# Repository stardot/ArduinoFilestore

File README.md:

# ArduinoFilestore
Build an Econet filestore out of an Arduino Due, an SD and Ethernet shield, and an Acorn Econet module.

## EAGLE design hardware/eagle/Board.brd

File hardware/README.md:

# Assembling the Arduino FileStore
The project is based around the [Arduino Due](https://store.arduino.cc/arduino-due) board, fitted with an SD card and Ethernet shield. The Due was chosen because of the combination of IO pin availability, and the speed of the 32Bit Arm processor on-board.

This is interfaced to an Acorn ADF10 (or AEH52) Econet module of the type normally used to upgrade a BBC Master, Acorn Archimedes or A Series machine with Econet connectivity. Only the Acorn upgrade cards have been tested and confirmed to work. The HCCS Econet module was found not to work when tested.

The Econet module and Arduino have their data bus linked via a SN74LVC245A buffer which provides the bidirectional 5 to 3.3 volt translation. Other inputs to the Econet module are driven directly by the Arduino, and the IRQ output from the Econet module has a pull down resistor to reduce the voltage to a safe level for the Arduino. 

The 2Mhz clock is generated by the CPU timers on the Arduino, and is left to free run once configured. I've not found a reliable way of determining the clock phase by reading the CPU registers, and so the clock signal is looped back into a input pin on the Arduino.

The Eagle folder contains the schematic and board layout I used to produce a run of PCBs for the project. This layout only really works with the ADF10 module which has the long pins, you would need to move the Econet card headers clear of the DIN socket to be able to use the AEH52 module which has shorter pins. 

The Gerbers folder contains an archive of the files I sent to jlcpcb to make the PCBs for the project.

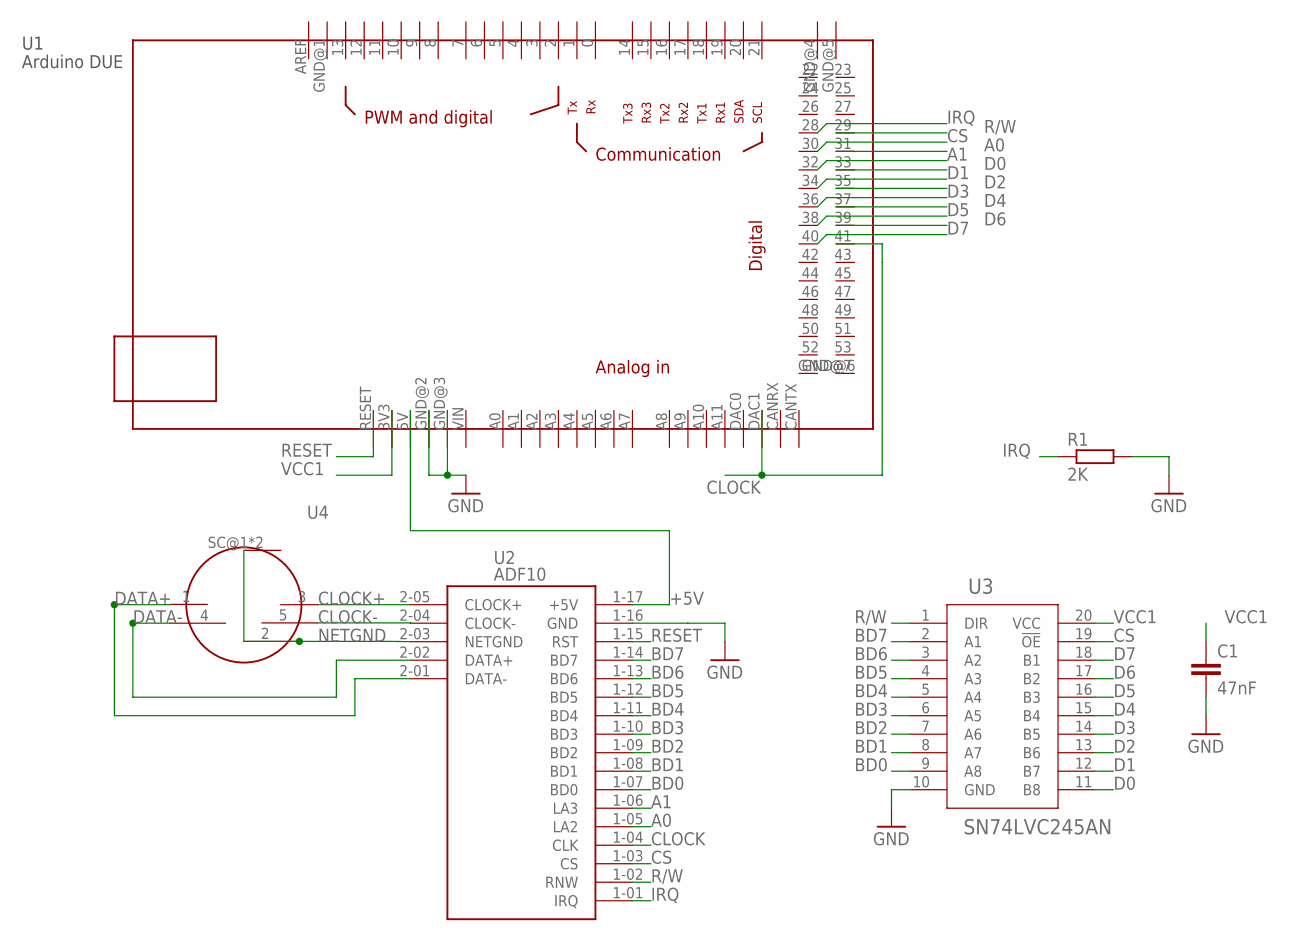
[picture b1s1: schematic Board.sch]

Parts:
C1: 47nF; C050-035X075
R1: 2K; 0309/12
U1: ARDUINODUE; MEGABOX
U2: ADF10
U3: SN74LVC245AN; N20
U4: 491087

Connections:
+5V: U1.5V, U2.1-17 (+5V)
A0: U1.31, U2.1-05 (LA2)
A1: U1.32, U2.1-06 (LA3)
BD0: U2.1-07 (BD0), U3.9 (A8)
BD1: U2.1-08 (BD1), U3.8 (A7)
BD2: U2.1-09 (BD2), U3.7 (A6)
BD3: U2.1-10 (BD3), U3.6 (A5)
BD4: U2.1-11 (BD4), U3.5 (A4)
BD5: U2.1-12 (BD5), U3.4 (A3)
BD6: U2.1-13 (BD6), U3.3 (A2)
BD7: U2.1-14 (BD7), U3.2 (A1)
CLOCK: U1.41, U1.DAC1, U2.1-04 (CLK)
CLOCK+: U2.2-05 (CLOCK+), U4.3
CLOCK-: U2.2-04 (CLOCK-), U4.5
CS: U1.30, U2.1-03 (CS), U3.19 (!OE)
D0: U1.33, U3.11 (B8)
D1: U1.34, U3.12 (B7)
D2: U1.35, U3.13 (B6)
D3: U1.36, U3.14 (B5)
D4: U1.37, U3.15 (B4)
D5: U1.38, U3.16 (B3)
D6: U1.39, U3.17 (B2)
D7: U1.40, U3.18 (B1)
DATA+: U2.2-01 (DATA-), U4.1
DATA-: U2.2-02 (DATA+), U4.4
GND: C1.2, R1.2, U1.GND@2 (GND), U1.GND@3 (GND), U2.1-16 (GND), U3.10 (GND)
IRQ: R1.1, U1.28, U2.1-01 (IRQ)
NETGND: U2.2-03 (NETGND), U4.2, U4.SC@1 (SHIELD), U4.SC@2 (SHIELD)
R/W: U1.29, U2.1-02 (RNW), U3.1 (DIR)
RESET: U1.RESET, U2.1-15 (RST)
VCC1: C1.1, U1.3V3, U3.20 (VCC)

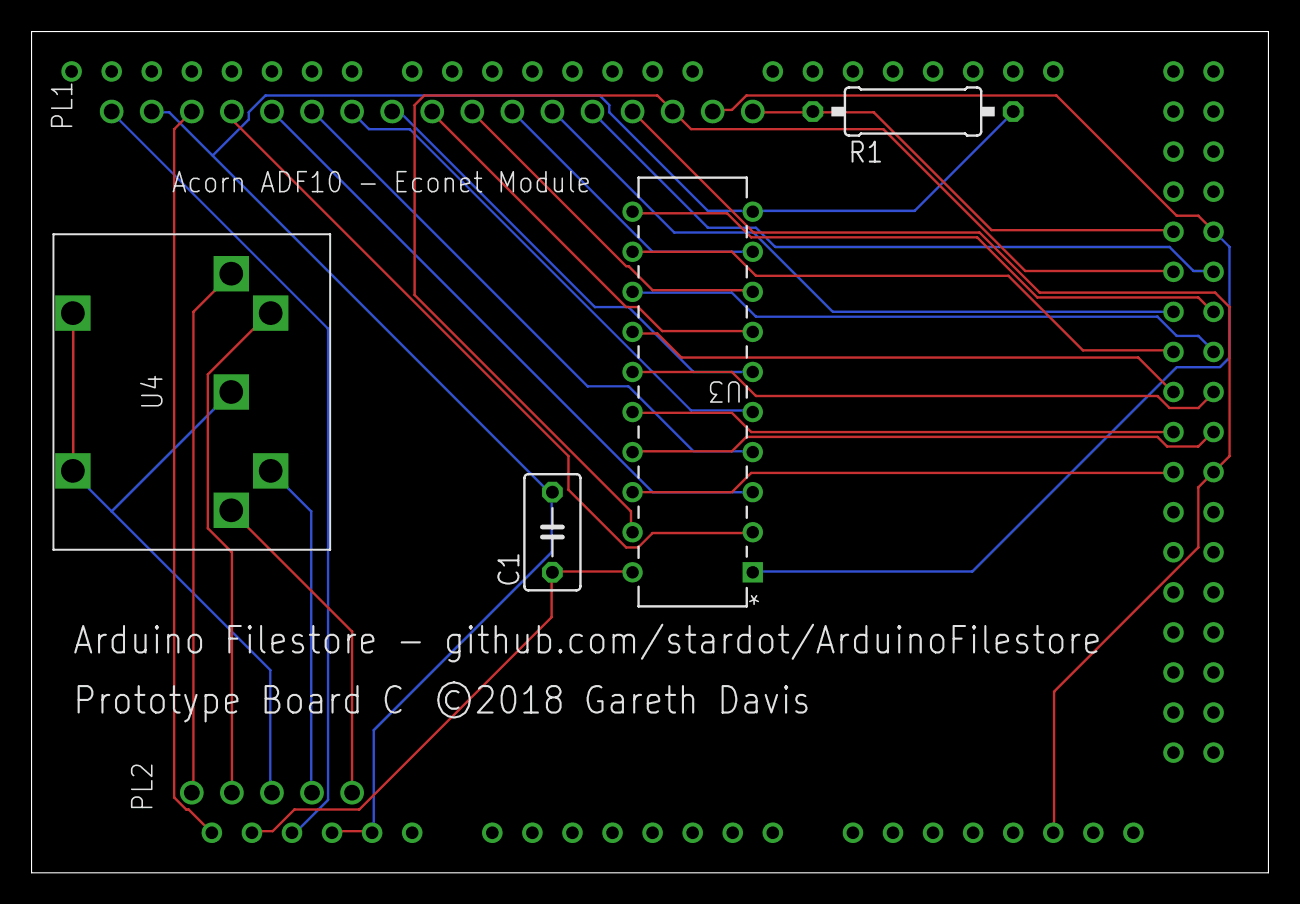
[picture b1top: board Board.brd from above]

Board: 2 copper layers, 78.4 x 53.3 mm, 6 parts (0 on the bottom side), 31 nets.

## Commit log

2018-03-31 schematic drawing
2018-03-31 First code upload
2018-03-31 Create README.md
    Build information
2018-03-31 Create LICENSE
2018-04-14 Updated LoadAs
    LoadAs incorrectly using CSD path instead of filehandle passed as CSD.
2018-06-22 Adjusted timeouts, and dropped CSD and lib handle caching.
    Amended protocol timeouts and associated error messages
    Removed internal caching of CSD and Library handles per user, now the handles in the TX header are always used.
2018-06-23 Added back in setURD during login removed in error in last commit
2018-06-23 Fixed typos
2018-07-15 Fixing of bugs #2 and #15
    Fixing of bugs #2 and #15 by refactoring the parsing of logon parameters.
2018-07-16 Added access control
    Added enforcement of public and owner file access attributes, and directory access rules from #17
2018-07-22 Examine not returning & #19
    Implimented missing function
2018-07-22 Fix for insufficient access when creating file #20
    Added case to provide default attributes when querying against a non existant file
2018-07-22 Fix for #18
2018-07-22 Fix for #21
    Added correct behaviour for *DIR and *LIB when executed without a parameter
2018-07-22 Updated implementation details
2018-09-10 Uploaded hardware schematics and gerber files.
2018-12-01 Added FSSHUTDOWN and FSREBOOT commands, and started code refactor for #16
2018-12-16 Additional refactoring of hardcoded config values
    Config defaults moved to top of code.
    Station config moved to a byte, to allow removal of additional toInt() steps that were affecting program timings.
    Also version of Arduino IDE changed, which has introduced numerous formatting changes.
2018-12-16 Additional commits against #16, all IP settings now held on disk.
    MAC address, IP, Netmask, Gateway, DNS and NTP server settings now held on disk.
    Defaults to MAC address based on Econet station, and DHCP for other IP settings if no disk config found.
2018-12-16 Added details of config folder to docs
2018-12-16 Fixed typo
2019-01-06 Changes to diagnose frame timing issues
    Made timeout to receive an ACK during tx configurable, and report ack timeouts to console.
    Altered existing timeout to closer match those RISCOS NetFS uses by default
    Added additional debug message when FS operation complete.
2019-01-06 Reduce privs of fixed and locked users #23
    User privilege now cached in memory
    Fixed and Locked users now unable to set password, or call function 22 (set boot options)
2019-01-06 Fixed multiple regressions discovered in #22
2019-01-06 Fixed further regressions identified in #22
    Enforcement of rights on file open and create now working again.
2019-01-06 Fixed LoadAs function
    Function was not checking the correct library path, nor enforcing permissions correctly.
2019-01-07 LoadAs symantics modified, console cleanup
    LoadAs function updated to match the error symantics of Level 4
    A couple of console messages truncated to improve the readibility
2019-01-07 Fixes for Set Attributes not working on preexisting folders #25
    createMetaFile being called with metafile path, not object path.
    Refactored code to store metafile and object path in different strings.
2019-01-07 Fixes for a number of cases where ownership of objects was not correctly determined #26
2019-01-08 Fix for loss of file attributes when saving file
2019-01-26 Added *SDISC command, made changes to error reporting
    *SDISC command added, so it's now possible to complete a base NetFS installation on PANOS on the server.
    Also automatic frame TX retries are no longer reported on in server console. Frequent seem to be normal behaviour in an Econet environment, and the client side NetFS interface also does not report th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
    Also the network buffer has been raised form 4K to 16K, which improves throughput of larger files on RISC OS machines
2019-03-31 Enabled debugging on config persistence
2019-03-31 Fix for #31, enable BYE from OSCLI interface
2019-03-31 Enhancement #30, added OSCLI CDIR support
2019-03-31 Added missing format to Examine object command
2019-03-31 Added *INFO and *i. OSCLI commands for MOS machines #12
2019-03-31 Comment tidy up
2019-03-31 Added new command *FSSTATUS to examine saved config #16 , also removed only non string from config
2019-03-31 Added FSCONFIGURE command to allow persistent config to be set remotely #16
2019-03-31 Write configuration defaults when set
    Write configuration defaults to file when they are applied, this is to allow them to be changed by *FSCONFIGURE
2019-03-31 Provided new details of config folder management
2020-03-09 Folded the Scout and data tx routines into one
2020-03-09 Timeout changes
2020-03-09 Changes to error messages
2020-03-10 Network idle resets scout received state, ignore unexpected packets
2020-03-10 Removed commented out code
2020-03-28 Removed the writing of invalid config defaults on startup for #31
    Also fixed the message shown when the Gateway is defaulted
2020-03-28 Revert "Removed the writing of invalid config defaults on startup for #31"
    This reverts commit 6e38d3a6dea326da694635208e97cba288cf9fef.
2020-03-28 Revert "Revert "Removed the writing of invalid config defaults on startup for #31""
    This reverts commit 4abd7b5405f040525f10b5735e2f2e8074743089.
2020-03-28 Revert "Revert "Revert "Removed the writing of invalid config defaults on startup for #31"""
    This reverts commit 535b87392e50063b2e5b00f3dca96ab672ca1909.
2020-03-28 Fix for #34
2020-03-28 Fix for #33
2020-03-28 Remove incorrect writeback of default config options #34
2020-03-28 Updated refrence to logon issues
2020-03-29 Timing tweaks
2020-03-29 Addition of *LOGOFF manager command #13
2020-03-29 Moved protocol settings to config files #16
2020-03-31 Implementation of #10
2020-03-31 Implementation of #7
2020-04-01 Refactor of initial config values for #35
2020-04-11 Added framework for AUN UDP packet reception
2020-04-11 Fixed post compile typo
2020-04-12 Added checking of net byte on reception for #36
2020-04-12 Added AUN immediate operation support #27
    Also moved large strings to flash.
2020-04-12 Fixed AUN packet display looking at wrong buffer
2020-04-13 First cut of AUN packet TX and RX routines for #27
2020-04-13 Freeway broadcast suppression for #38
2020-04-13 Changes to port allocation for #37
2020-04-13 Added AUN network table #27
2020-04-13 Tidying up of console messages
2020-04-14 Console alignment
2020-04-19 Added AUN packet size limits for #39 and some additional debug
2020-04-19 AUN implementation changes, and fix to machinepeek version
2020-05-03 Changes to debug messages
2020-05-03 Numerous timing changes to improve relability
2020-05-03 Packet size fix for #41
2020-05-03 Cap Econet packet size for get bytes to 4K #41
2020-05-03 Tweaks to error messages, and fix for fsshutdown waking up.
2020-05-04 Fix for bulk transfers sometimes sending more bytes than expected #42, and additional debug
2020-05-05 Additional debug statemants and rework of put bytes for #44
2020-05-05 Formatting change
2020-05-08 Changes to econet max frame logic for #45
2020-05-09 Bulk TX now written to disk after successful acknowledgement #44
2020-05-09 Updated packet size setting on save to match put bytes #45
2020-05-11 Added missing & folder handling #43
2020-05-11 Changed position of & rewrite in logic flow to benefit all functions #43
2020-05-11 Chroot for fixed users, and & reliative paths #23
2020-05-13 Implmented action 1 on Set Random Access Args, plus other fixes for #44
2020-05-13 Fixes for #46 - zero byte save failing
2020-05-13 Compiler alignment bug workaround
2020-06-14 Fix for $ mapping for fixed users #47
2020-06-14 Reduced verbosity of common failures
2020-06-14 Added W5500 card detection, bumped RTC to Econet Epoch if fails to sync with NTP
2020-06-14 Added AUN map support with fixed default table #40
2020-08-05 Synced hardware schematic with Eagle files

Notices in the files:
hardware/eagle/Board.brd:
©2018 Gareth Davis
